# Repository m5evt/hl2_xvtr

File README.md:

# hl2_xvtr

Hermes-Lite 2 transverter companion card

Designed with the same footprint as the N2ADR filter board, this companion card is to be coupled to the Hermes-Lite 2 SDR transceiver. The transverter clock is designed to be sourced from the HL2 clock outputs. Power output is around 20 dBm and an amplifier will need to be used with this. 

The design has been built and tested on both 6m and 2m.

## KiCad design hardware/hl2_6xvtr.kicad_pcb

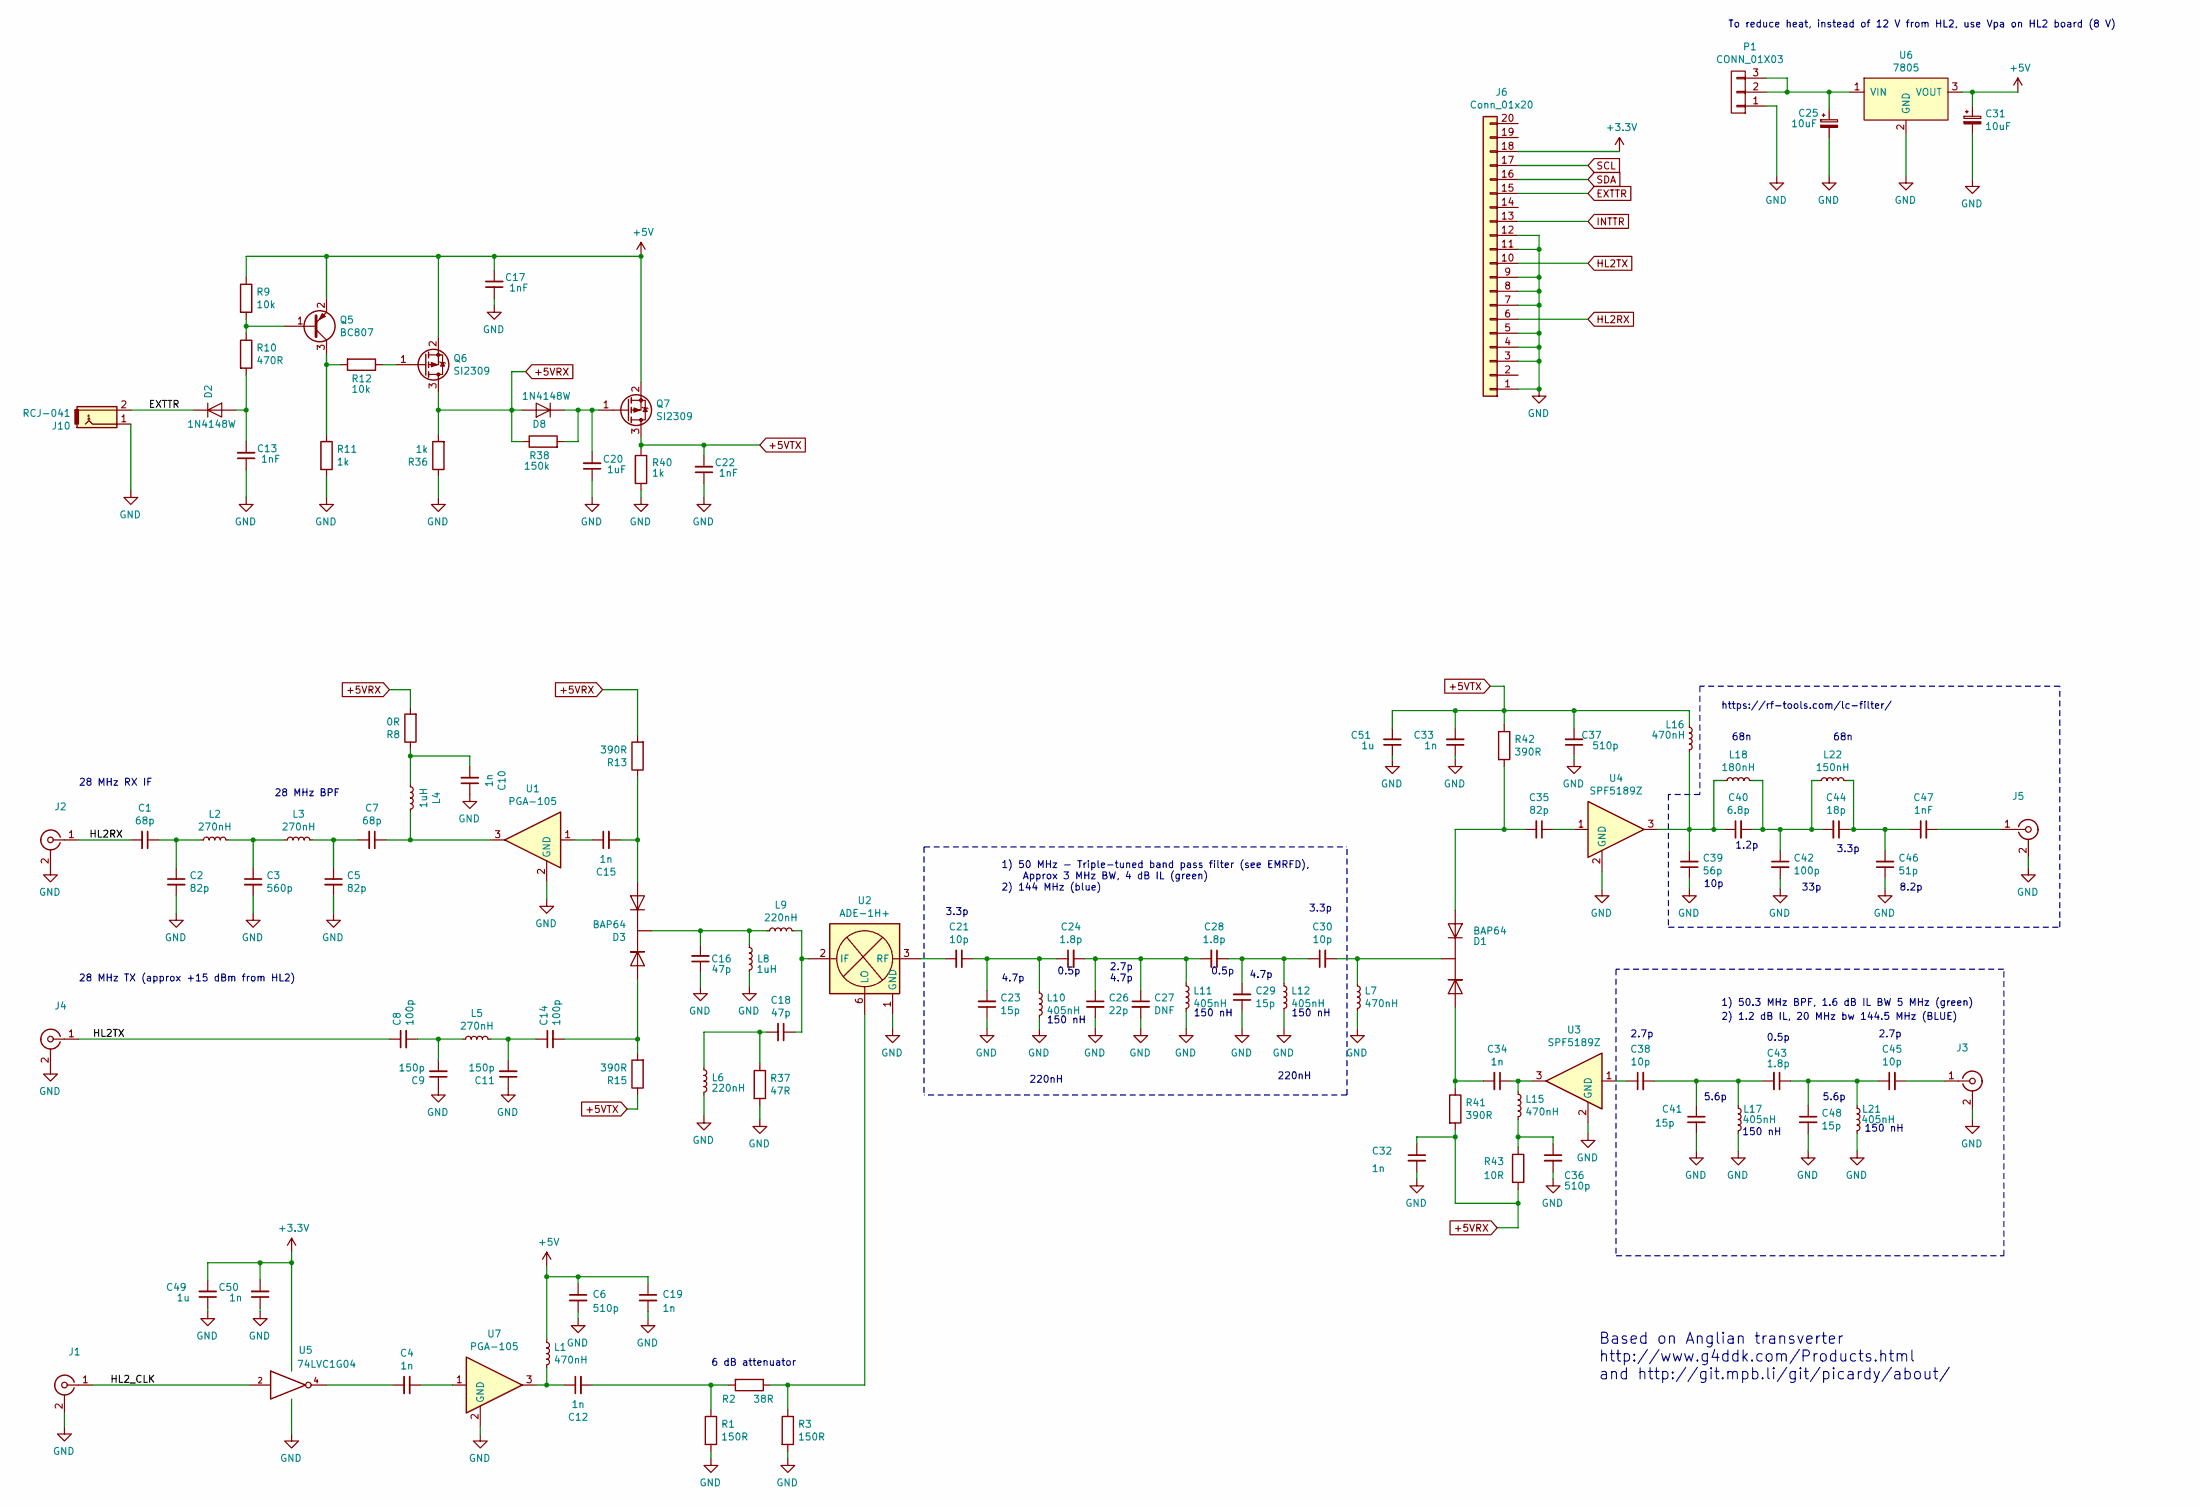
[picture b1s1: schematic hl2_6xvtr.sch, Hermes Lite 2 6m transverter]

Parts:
C1, C7: 68p; SMD-0603_c
C2, C5, C35: 82p; SMD-0603_c
C3: 560p; SMD-0603_c
C4, C10, C12, C15, C19, C32, C33, C34, C50: 1n; SMD-0603_c
C6, C36, C37: 510p; SMD-0603_c
C8, C14, C42: 100p; SMD-0603
C9, C11: 150p; SMD-0603_c
C13, C17, C22, C47: 1nF; SMD-0603_c
C16, C18: 47p; SMD-0603_c
C20: 1uF; SMD-0603_c
C21, C30, C38, C45: 10p; SMD-0603_c
C23, C29, C41, C48: 15p; SMD-0603_c
C24, C28, C43: 1.8p; SMD-0603_c
C25, C31: 10uF; CP_Elec_5x5.4
C26: 22p; SMD-0603_c
C27: DNF; SMD-0603_c
C39: 56p; SMD-0603_c
C40: 6.8p; SMD-0603_c
C44: 18p; SMD-0603_c
C46: 51p; SMD-0603_c
C49, C51: 1u; SMD-0603_c
D1, D3: BAP64; SOT23_3
D2, D8: 1N4148W; D_SOD-123
J1: Conn_Coaxial-Connector; U.FL_Hirose_U.FL-R-SMT-1_Vertical
J2, J3, J4, J5: Conn_Coaxial-Connector; BNCEDGE
J6: Conn_01x20; PinSocket_1x20_P2.54mm_Vertical
J10: RCJ-041; PhonoRcaRCJ-04x
L1, L7, L15, L16: 470nH; SMD-0805
L2, L3, L5: 270nH; SMD-0805
L4, L8: 1uH; SMD-0805
L6, L9: 220nH; SMD-0805
L10, L11, L12, L17, L21: 405nH; coilcraft_tunable_coil
L18: 180nH; SMD-0805
L22: 150nH; SMD-0805
P1: CONN_01X03; PinSocket_1x03_P2.54mm_Vertical
Q5: BC807; SOT-23
Q6, Q7: SI2309; SOT-23
R1, R3: 150R; SMD-0805
R2: 38R; SMD-0805
R8: 0R; SMD-0603_r
R9, R12: 10k; SMD-0603_r
R10: 470R; SMD-0603_r
R11, R36, R40: 1k; SMD-0603_r
R13, R15, R41, R42: 390R; SMD-0603_r
R37: 47R; SMD-0603_r
R38: 150k; SMD-0603_r
R43: 10R; SMD-0603_r
U1, U7: PGA-105; SOT-89-3_round
U2: ADE-1H+; Mini-Circuits_CD542_LandPatternPL-052
U3, U4: SPF5189Z; SOT-89-3_round
U5: 74LVC1G04; SOT-353_SC-70-5_Handsoldering
U6: 7805; TO-263-2

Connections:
+3V3: C49.2, C50.2, J6.18, U5.5 (VCC)
+5V: C6.1, C17.2, C19.1, C31.1, L1.1, Q5.2 (E), Q6.2 (S), Q7.2 (S), R9.1, U6.3 (VOUT)
+5VRX: C32.1, D8.2 (A), Q6.3 (D), R8.2, R13.2, R36.2, R38.1, R41.2, R43.2
+5VTX: C22.2, C33.2, C37.2, C51.2, L16.1, Q7.3 (D), R15.1, R40.1, R42.1
/HL2_CLK: J1.1 (In), U5.2
EXTTR: D2.1 (K), J6.15, J10.2
GND: C2.2, C3.2, C5.2, C6.2, C9.1, C10.1, C11.1, C13.1, C16.1, C17.1, C19.2, C20.1, C22.1, C23.1, C25.2, C26.2, C27.2, C29.1, C31.2, C32.2, C33.1, C36.2, C37.1, C39.1, C41.2, C42.2, C46.1, C48.2, C49.1, C50.1, C51.1, J1.2 (Ext), J2.2 (Ext), J3.2 (Ext), J4.2 (Ext), J5.2 (Ext), J6.1, J6.3, J6.4, J6.5, J6.7, J6.8, J6.9, J6.11, J6.12, J10.1, L6.2, L7.2, L8.2, L10.2, L11.2, L12.2, L17.1, L21.1, P1.1, R1.2, R3.2, R11.2, R36.1, R37.2, R40.2, U1.2 (GND), U2.1 (GND), U2.4 (GND), U2.5 (GND), U3.2 (GND), U4.2 (GND), U5.3 (GND), U6.2 (GND), U7.2 (GND)
HL2RX: C1.2, J2.1 (In), J6.6
HL2TX: C8.1, J4.1 (In), J6.10
INTTR: J6.13
unnamed: C1.1, C2.1, L2.1
unnamed: C3.1, L2.2, L3.1
unnamed: C4.1, U7.1
unnamed: C4.2, U5.4
unnamed: C5.1, C7.2, L3.2
unnamed: C7.1, L4.2, U1.3
unnamed: C8.2, C9.2, L5.1
unnamed: C10.2, L4.1, R8.1
unnamed: C11.2, C14.1, L5.2
unnamed: C12.1, L1.2, U7.3
unnamed: C12.2, R1.1, R2.2
unnamed: C13.2, D2.2 (A), R10.2
unnamed: C14.2, D3.1 (A), R15.2
unnamed: C15.1, U1.1
unnamed: C15.2, D3.2 (A), R13.1
unnamed: C16.2, D3.3 (K), L8.1, L9.1
unnamed: C18.1, L9.2, U2.2 (IF)
unnamed: C18.2, L6.1, R37.1
unnamed: C20.2, D8.1 (K), Q7.1 (G), R38.2
unnamed: C21.1, C23.2, C24.1, L10.1
unnamed: C21.2, U2.3 (RF)
unnamed: C24.2, C26.1, C27.1, C28.2, L11.1
unnamed: C25.1, P1.2, P1.3, U6.1 (VIN)
unnamed: C28.1, C29.2, C30.1, L12.1
unnamed: C30.2, D1.3 (K), L7.1
unnamed: C34.1, L15.1, U3.3
unnamed: C34.2, D1.1 (A), R41.1
unnamed: C35.1, U4.1
unnamed: C35.2, D1.2 (A), R42.2
unnamed: C36.1, L15.2, R43.1
unnamed: C38.1, U3.1
unnamed: C38.2, C41.1, C43.2, L17.2
unnamed: C39.2, C40.1, L16.2, L18.1, U4.3
unnamed: C40.2, C42.1, C44.2, L18.2, L22.1
unnamed: C43.1, C45.1, C48.1, L21.2
unnamed: C44.1, C46.2, C47.1, L22.2
unnamed: C45.2, J3.1 (In)
unnamed: C47.2, J5.1 (In)
unnamed: Q5.1 (B), R9.2, R10.1
unnamed: Q5.3 (C), R11.1, R12.2
unnamed: Q6.1 (G), R12.1
unnamed: R2.1, R3.1, U2.6 (LO)
SCL: J6.17
SDA: J6.16

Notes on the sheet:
Based on Anglian transverter http://www.g4ddk.com/Products.html and http://git.mpb.li/git/picardy/about/
28 MHz RX IF
28 MHz TX (approx +15 dBm from HL2)
1) 50.3 MHz BPF, 1.6 dB IL BW 5 MHz (green)
28 MHz BPF
1) 50 MHz - Triple-tuned band pass filter (see EMRFD), Approx 3 MHz BW, 4 dB IL (green) 2) 144 MHz (blue)
https://rf-tools.com/lc-filter/
To reduce heat, instead of 12 V from HL2, use Vpa on HL2 board (8 V)
6 dB attenuator
2.7p
5.6p
0.5p
150 nH
10p
33p
8.2p
3.3p
1.2p
68n
2) 1.2 dB IL, 20 MHz bw 144.5 MHz (BLUE)
2.7p 4.7p
4.7p
220nH

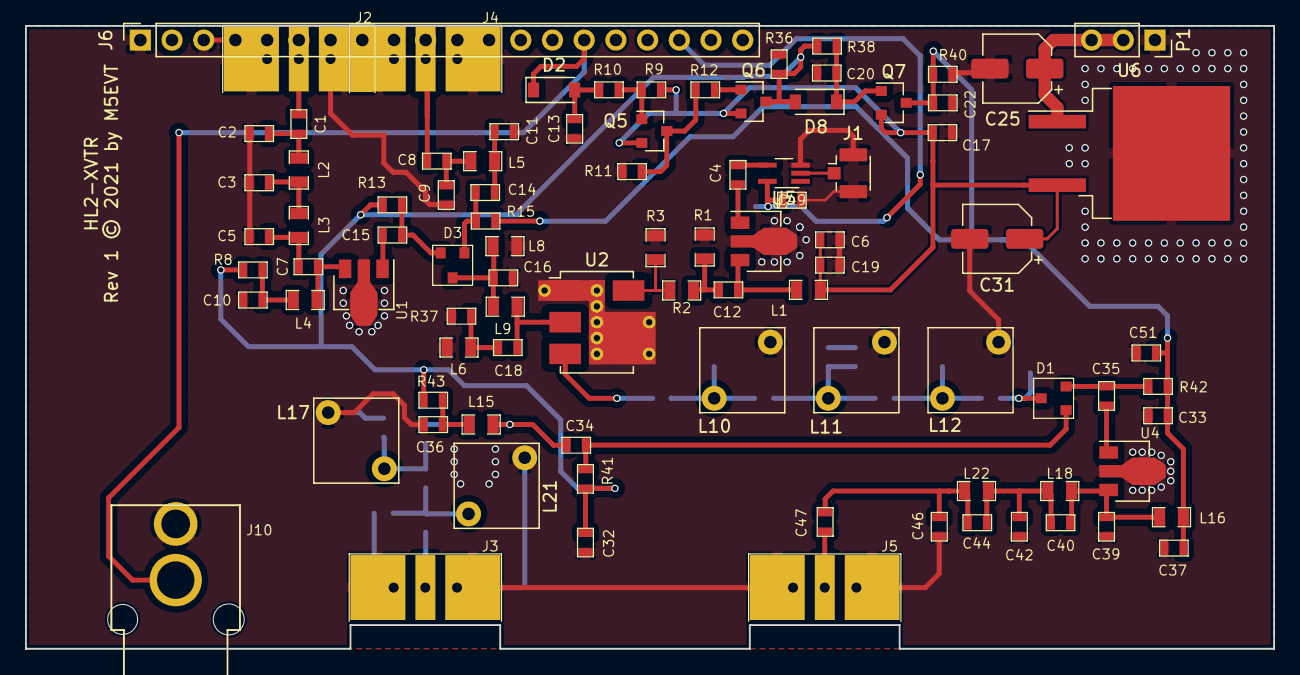
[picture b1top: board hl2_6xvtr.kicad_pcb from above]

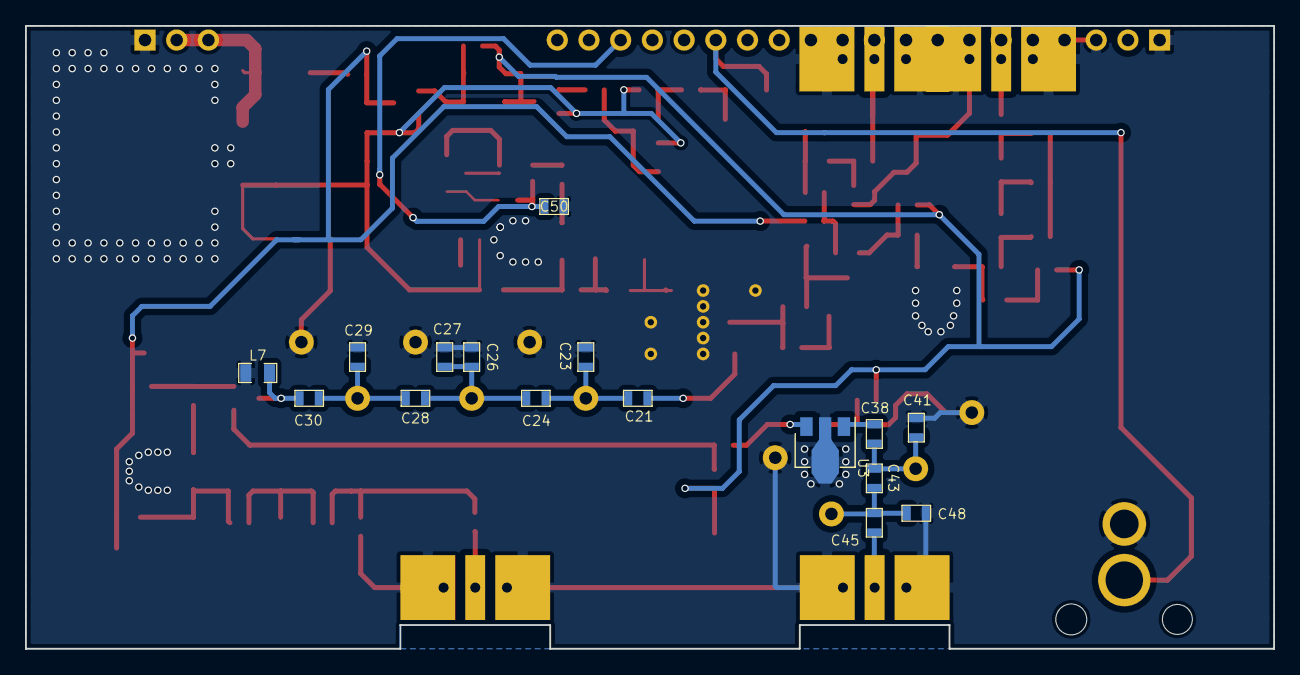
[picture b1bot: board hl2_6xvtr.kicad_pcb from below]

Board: 2 copper layers, 100.0 x 49.9 mm, 108 parts (16 on the bottom side), 51 nets.

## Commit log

2021-09-05 Fixes #6, #2, partial #1, #4
2021-09-05 R2 schem, PCB and gerbers
    Fixes #1, fixes #4, fixes #5
2021-09-05 Fix gerber zip
2021-10-27 Add 2m component values to schematic and BoM
2021-10-27 Add bpf measurements
2021-10-27 Add images to readme

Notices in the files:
hardware/hl2_6xvtr.kicad_pcb:
Rev 1 © 2021 by M5EVT
